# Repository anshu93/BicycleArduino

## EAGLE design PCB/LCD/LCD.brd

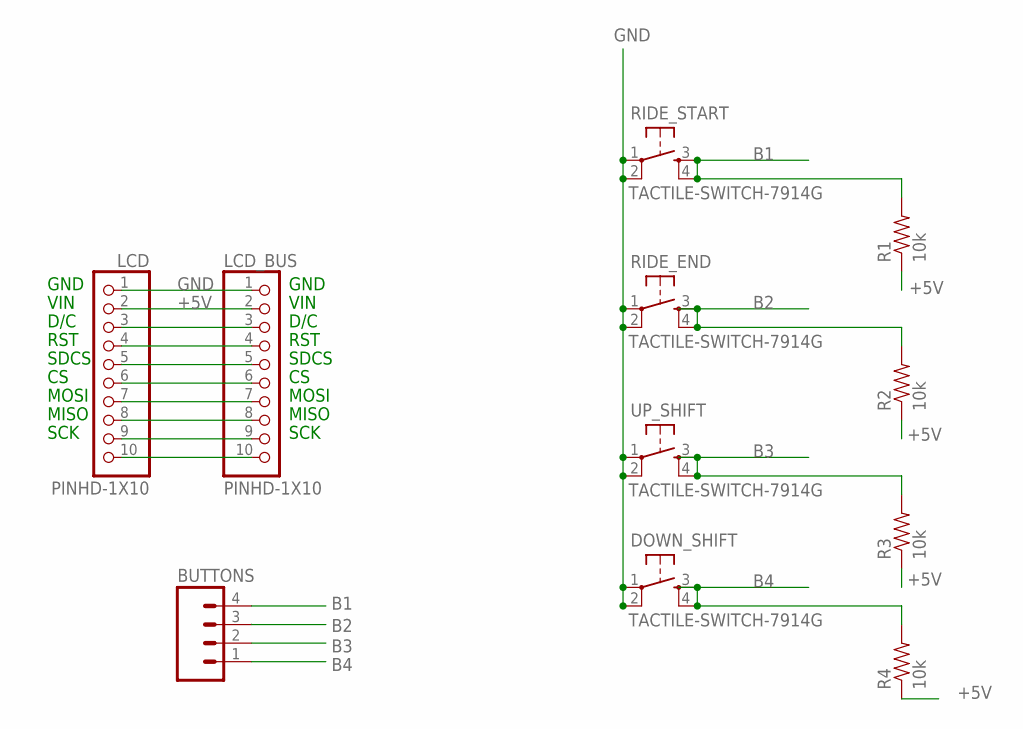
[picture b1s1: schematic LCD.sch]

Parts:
BUTTONS: M04LONGPADS; 1X04_LONGPADS
DOWN_SHIFT: TACTILE-SWITCH-7914G; 7914G
LCD: PINHD-1X10; 1X10-BIG
LCD_BUS: PINHD-1X10; 1X10-BIG
R1, R2, R3, R4: 10k; 0805
RIDE_END: TACTILE-SWITCH-7914G; 7914G
RIDE_START: TACTILE-SWITCH-7914G; 7914G
UP_SHIFT: TACTILE-SWITCH-7914G; 7914G

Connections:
+5V: LCD.2, LCD_BUS.2, R1.1, R2.1, R3.1, R4.1
B1: BUTTONS.4, R1.2, RIDE_START.3, RIDE_START.4
B2: BUTTONS.3, R2.2, RIDE_END.3, RIDE_END.4
B3: BUTTONS.2, R3.2, UP_SHIFT.3, UP_SHIFT.4
B4: BUTTONS.1, DOWN_SHIFT.3, DOWN_SHIFT.4, R4.2
GND: DOWN_SHIFT.1, DOWN_SHIFT.2, LCD.1, LCD_BUS.1, RIDE_END.1, RIDE_END.2, RIDE_START.1, RIDE_START.2, UP_SHIFT.1, UP_SHIFT.2
unnamed: LCD.3, LCD_BUS.3
unnamed: LCD.4, LCD_BUS.4
unnamed: LCD.5, LCD_BUS.5
unnamed: LCD.6, LCD_BUS.6
unnamed: LCD.7, LCD_BUS.7
unnamed: LCD.8, LCD_BUS.8
unnamed: LCD.9, LCD_BUS.9
unnamed: LCD.10, LCD_BUS.10

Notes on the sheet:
GND
VIN
RST
SDCS
MOSI
MISO
SCK
D/C

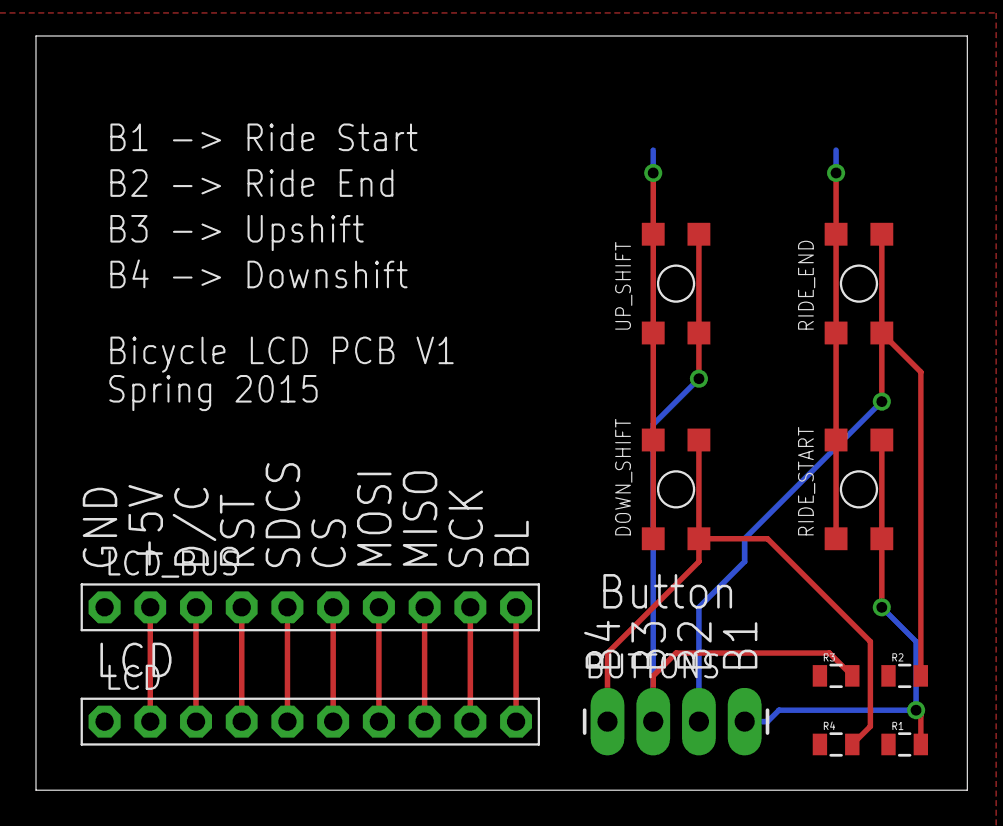
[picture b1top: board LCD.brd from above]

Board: 2 copper layers, 51.7 x 41.9 mm, 11 parts (0 on the bottom side), 14 nets.

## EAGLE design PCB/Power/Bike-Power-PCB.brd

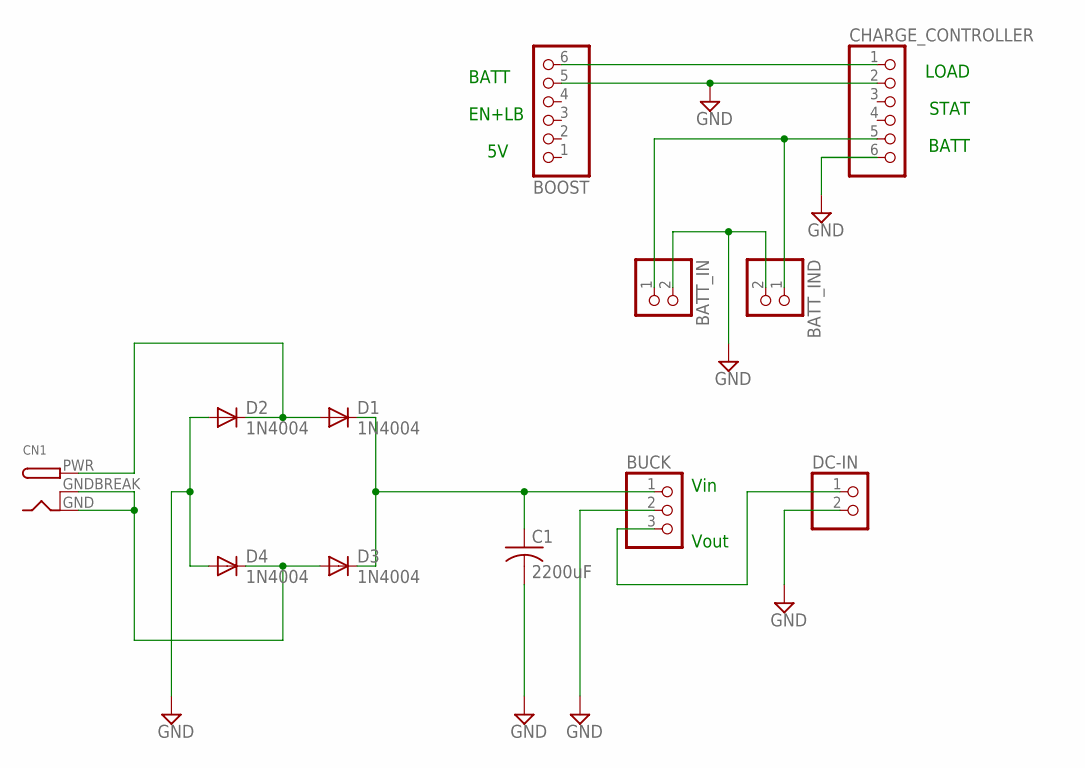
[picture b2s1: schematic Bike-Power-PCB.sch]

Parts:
BATT_IN: JST_2PIN-SMT-RA; JST-PH-2-SMT-RA
BATT_IND: PINHD-1X2; 1X02
BOOST: PINHD-1X6; 1X06
BUCK: PINHD-1X3; 1X03
C1: 2200uF; C0805
CHARGE_CONTROLLER: PINHD-1X6; 1X06
CN1: DCBARRELPTH; DCJACK_2MM_PTH
D1, D2, D3, D4: 1N4004; DO41-10
DC-IN: PINHD-1X2; 1X02

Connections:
GND: BATT_IN.2 (1), BATT_IND.2, BOOST.5, BUCK.2, C1.2, CHARGE_CONTROLLER.2, CHARGE_CONTROLLER.6, D2.A, D4.A, DC-IN.2
unnamed: BUCK.1, C1.1, D1.C, D3.C
unnamed: CN1.GND, CN1.GNDBREAK, D3.A, D4.C
unnamed: CN1.PWR, D1.A, D2.C
unnamed: BUCK.3, DC-IN.1
unnamed: BATT_IN.1 (2), BATT_IND.1, CHARGE_CONTROLLER.5
unnamed: BOOST.6, CHARGE_CONTROLLER.1

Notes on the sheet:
LOAD
STAT
BATT
EN+LB
Vin
Vout

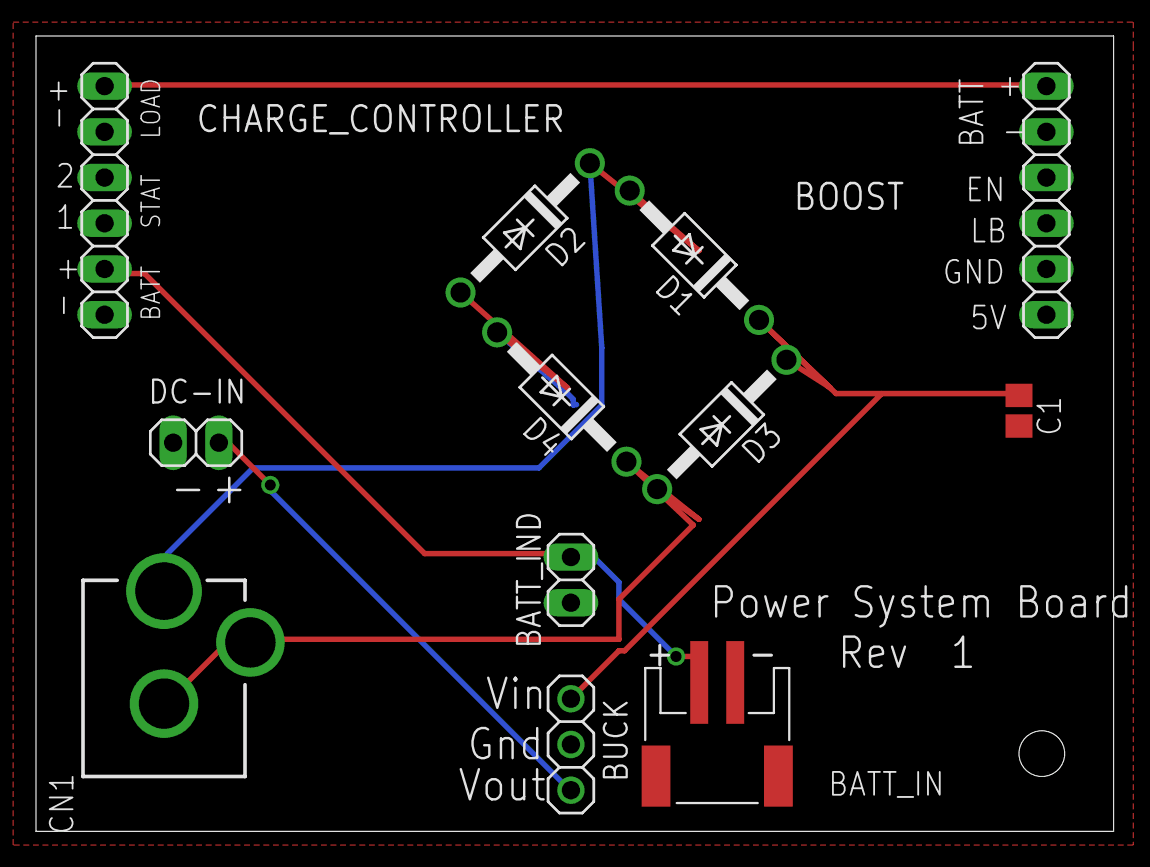
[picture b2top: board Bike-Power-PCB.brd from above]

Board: 2 copper layers, 59.9 x 44.2 mm, 12 parts (0 on the bottom side), 7 nets.

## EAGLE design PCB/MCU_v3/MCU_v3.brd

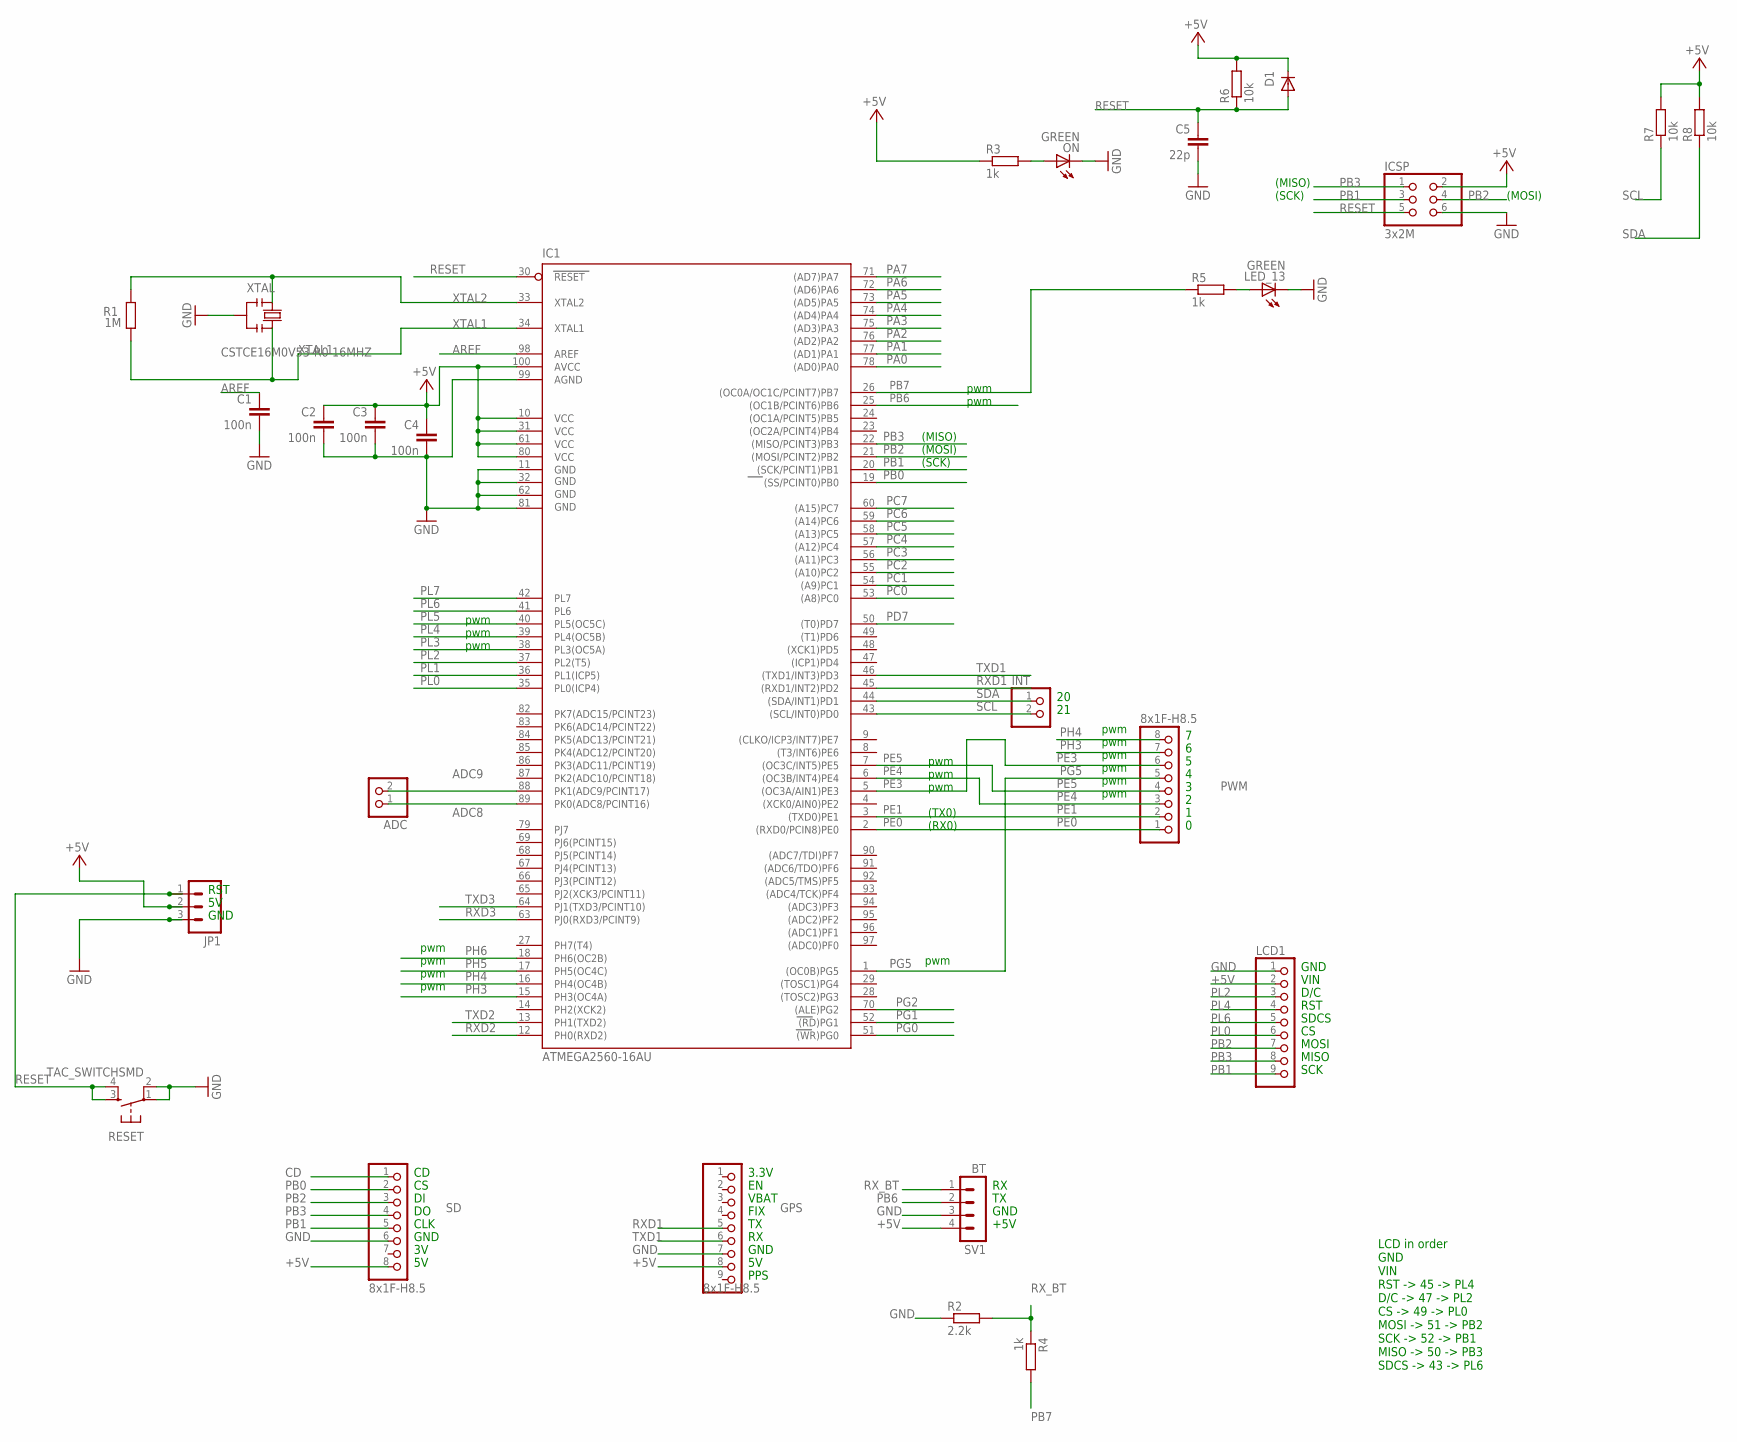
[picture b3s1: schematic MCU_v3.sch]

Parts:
ADC: PINHD-1X2; 1X02; MPN A21-X0-22-507-115-E
C1, C2, C3, C4: 100n; C0805
C5: 22p; C0805
D1: DIODE-MINIMELF; MINIMELF
GPS: 8x1F-H8.5; 1X09
IC1: ATMEGA2560-16AU; TQFP100
ICSP: 3x2M; 2X03
INT: PINHD-1X2; 1X02; MPN A21-X0-22-507-115-E
JP1: M03PTH; 1X03; MPN BI2-Q10S-AZ31X-0.3M-SB3T
LCD1: PINHD-1X9; 1X09
LED_13: GREEN; CHIP-LED0805
ON: GREEN; CHIP-LED0805
PWM: 8x1F-H8.5; 1X08
R1: 1M; R0805
R2: 2.2k; R0805
R3, R4, R5: 1k; R0805
R6, R7, R8: 10k; R0805
RESET: TAC_SWITCHSMD; TACTILE-SWITCH-SMD
SD: 8x1F-H8.5; 1X08
SV1: BT; MA04-1
XTAL: CSTCE16M0V53-R0 16MHZ; RESONATOR

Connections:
+5V: C2.1, C3.1, C4.1, D1.C, GPS.8, IC1.10 (VCC), IC1.31 (VCC1), IC1.61 (VCC2), IC1.80 (VCC3), IC1.100 (AVCC), ICSP.2, JP1.2, LCD1.2, R3.1, R6.2, R7.2, R8.2, SD.8, SV1.4
ADC8: ADC.1, IC1.89 (PK0(ADC8/PCINT16))
ADC9: ADC.2, IC1.88 (PK1(ADC9/PCINT17))
AREF: C1.1, IC1.98 (AREF)
CD: SD.1
GND: C1.2, C2.2, C3.2, C4.2, C5.2, GPS.7, IC1.11 (GND), IC1.32 (GND1), IC1.62 (GND2), IC1.81 (GND3), IC1.99 (AGND), ICSP.6, JP1.3, LCD1.1, LED_13.C, ON.C, R2.1, RESET.1, RESET.2, SD.6, SV1.3, XTAL.2
unnamed: LED_13.A, R5.2
unnamed: ON.A, R3.2
PA0: IC1.78 ((AD0)PA0)
PA1: IC1.77 ((AD1)PA1)
PA2: IC1.76 ((AD2)PA2)
PA3: IC1.75 ((AD3)PA3)
PA4: IC1.74 ((AD4)PA4)
PA5: IC1.73 ((AD5)PA5)
PA6: IC1.72 ((AD6)PA6)
PA7: IC1.71 ((AD7)PA7)
PB0: IC1.19 ((SS/PCINT0)PB0), SD.2
PB1: IC1.20 ((SCK/PCINT1)PB1), ICSP.3, LCD1.9, SD.5
PB2: IC1.21 ((MOSI/PCINT2)PB2), ICSP.4, LCD1.7, SD.3
PB3: IC1.22 ((MISO/PCINT3)PB3), ICSP.1, LCD1.8, SD.4
PB6: IC1.25 ((OC1B/PCINT6)PB6), SV1.2
PB7: IC1.26 ((OC0A/OC1C/PCINT7)PB7), R4.2, R5.1
PC0: IC1.53 ((A8)PC0)
PC1: IC1.54 ((A9)PC1)
PC2: IC1.55 ((A10)PC2)
PC3: IC1.56 ((A11)PC3)
PC4: IC1.57 ((A12)PC4)
PC5: IC1.58 ((A13)PC5)
PC6: IC1.59 ((A14)PC6)
PC7: IC1.60 ((A15)PC7)
PD7: IC1.50 ((T0)PD7)
PE0: IC1.2 ((RXD0/PCIN8)PE0), PWM.1
PE1: IC1.3 ((TXD0)PE1), PWM.2
PE3: IC1.5 ((OC3A/AIN1)PE3), PWM.6
PE4: IC1.6 ((OC3B/INT4)PE4), PWM.3
PE5: IC1.7 ((OC3C/INT5)PE5), PWM.4
PG0: IC1.51 ((WR)PG0)
PG1: IC1.52 ((RD)PG1)
PG2: IC1.70 ((ALE)PG2)
PG5: IC1.1 ((OC0B)PG5), PWM.5
PH3: IC1.15 (PH3(OC4A)), PWM.7
PH4: IC1.16 (PH4(OC4B)), PWM.8
PH5: IC1.17 (PH5(OC4C))
PH6: IC1.18 (PH6(OC2B))
PL0: IC1.35 (PL0(ICP4)), LCD1.6
PL1: IC1.36 (PL1(ICP5))
PL2: IC1.37 (PL2(T5)), LCD1.3
PL3: IC1.38 (PL3(OC5A))
PL4: IC1.39 (PL4(OC5B)), LCD1.4
PL5: IC1.40 (PL5(OC5C))
PL6: IC1.41 (PL6), LCD1.5
PL7: IC1.42 (PL7)
RESET: C5.1, D1.A, IC1.30 (RESET), ICSP.5, JP1.1, R6.1, RESET.3, RESET.4
RXD1: GPS.5, IC1.45 ((RXD1/INT2)PD2)
RXD2: IC1.12 (PH0(RXD2))
RXD3: IC1.63 (PJ0(RXD3/PCINT9))
RX_BT: R2.2, R4.1, SV1.1
SCL: IC1.43 ((SCL/INT0)PD0), INT.2, R7.1
SDA: IC1.44 ((SDA/INT1)PD1), INT.1, R8.1
TXD1: GPS.6, IC1.46 ((TXD1/INT3)PD3)
TXD2: IC1.13 (PH1(TXD2))
TXD3: IC1.64 (PJ1(TXD3/PCINT10))
XTAL1: IC1.34 (XTAL1), R1.1, XTAL.3
XTAL2: IC1.33 (XTAL2), R1.2, XTAL.1

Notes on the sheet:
(SCK)
(MISO)
(MOSI)
pwm
(TX0)
(RX0)
CLK
GND
FIX
VBAT
3.3V
+5V
PPS
RST
LCD in order GND VIN RST -> 45 -> PL4 D/C -> 47 -> PL2 CS -> 49 -> PL0 MOSI -> 51 -> PB2 SCK -> 52 -> PB1 MISO -> 50 -> PB3 SDCS -> 43 -> PL6
VIN
SDCS
MOSI
MISO
SCK
D/C

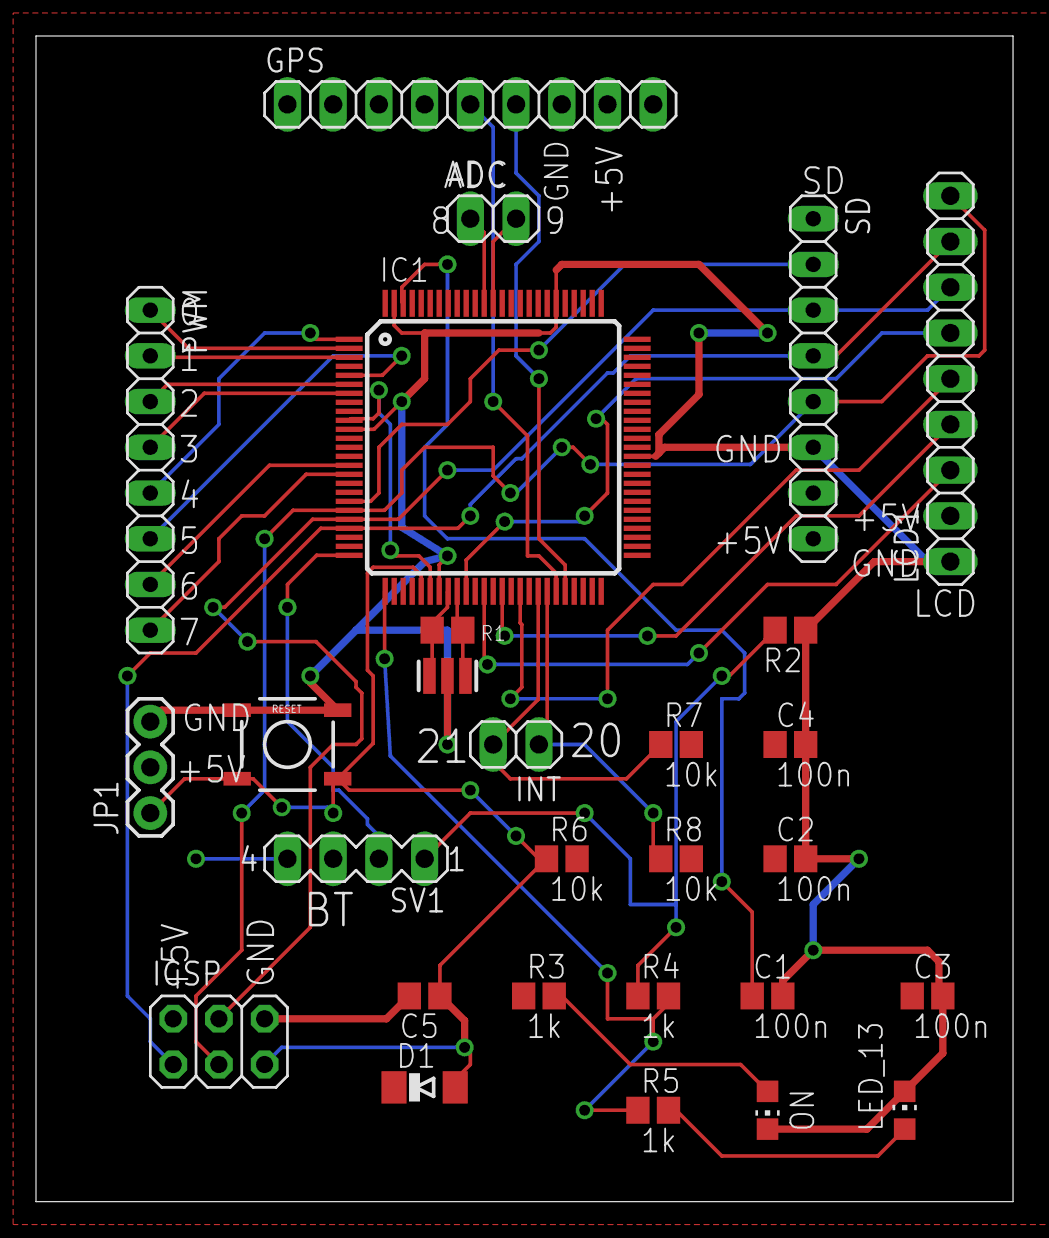
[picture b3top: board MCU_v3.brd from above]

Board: 2 copper layers, 54.3 x 64.8 mm, 28 parts (0 on the bottom side), 33 nets.

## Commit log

2015-02-05 RPM and bluetooth test with send/receive separately
2015-02-05 Integrated bluetooth and rpm readings and displayed to mobile app
2015-03-27 March 26th
2015-03-27 Medium gears sorted out
2015-04-03 RPM updated for all gear combinations

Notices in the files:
parts and their libraries:
SparkFun-Connectors: Licensing: Creative Commons ShareAlike 4.0 International - https://creativecommons.org/licenses/by-sa/4.0
